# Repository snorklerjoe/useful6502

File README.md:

# Useful 6502 Machine

The goal of this project is to build a 6502-based portable machine,
running my own operating system.

## Current Status

*See the complete implementation plan and progress here: [Implemementation Plan](./IMPLEMENTATION_PLAN.md)*

PCB assembled, PIC is able to load code for the 6502 to execute, the 6502 can read/write to the 2-port SRAM.

## Hardware Goals

*These are some general points; for the full hardware specification, see here: [Hardware Specification](./HARDWARE.md)*

I want the following end goals to categorize the machine as "useful":

- At least 2 Megabytes of program memory and 2 Megabytes of data memory, of which at least 16k of memory can be used by a single process.
- Protected memory (kernel and user run modes defined by hardware checking if kernel or user code is being executed)
- PIC16 as peripheral coprocessor for fast i/o

## Software Goals

- Traps via "BRK" instruction for sys calls
- Full preemptive multitasking with up to 255 processes, round robin scheduler (maybe mlfq eventually)
- Filesystem: Tree, leaf nodes are devices or drivers.
- Driver for FAT32-formatted SD cards for easy file storage & transfer
- Standard library compatible with cc65 for creating high-level programs
- Basic UNIX-like shell utilities
- Simple web browser?
- SSH client based on DropBear?

## Faults

Faults will be detected by hardware and trigger a RESET, and the kernel will terminate the process.

## Hardware Timers

A hardware timer using the 65c22 will be used to interrupt processes with an NMI.
The kernel will maintain a global clock for user timing needs.

The PIC peripheral coprocessor may, perhaps, feature a watchdog timer to restart the kernel in the event of a crash.

## Particularly Helpful References

There are many resources that have proven themselves indispensible to the progress of his project.  
Here is a *small subset* of such resources:

- <https://www.pagetable.com/c64ref/6502/#>
- <http://www.6502.org/users/andre/index.html>
- <https://wilsonminesco.com/>
- <https://www.burtonsys.com/ps2_chapweske.htm>
- <https://www.pagetable.com/?p=1416>
- <https://github.com/commanderx16/x16-rom/>

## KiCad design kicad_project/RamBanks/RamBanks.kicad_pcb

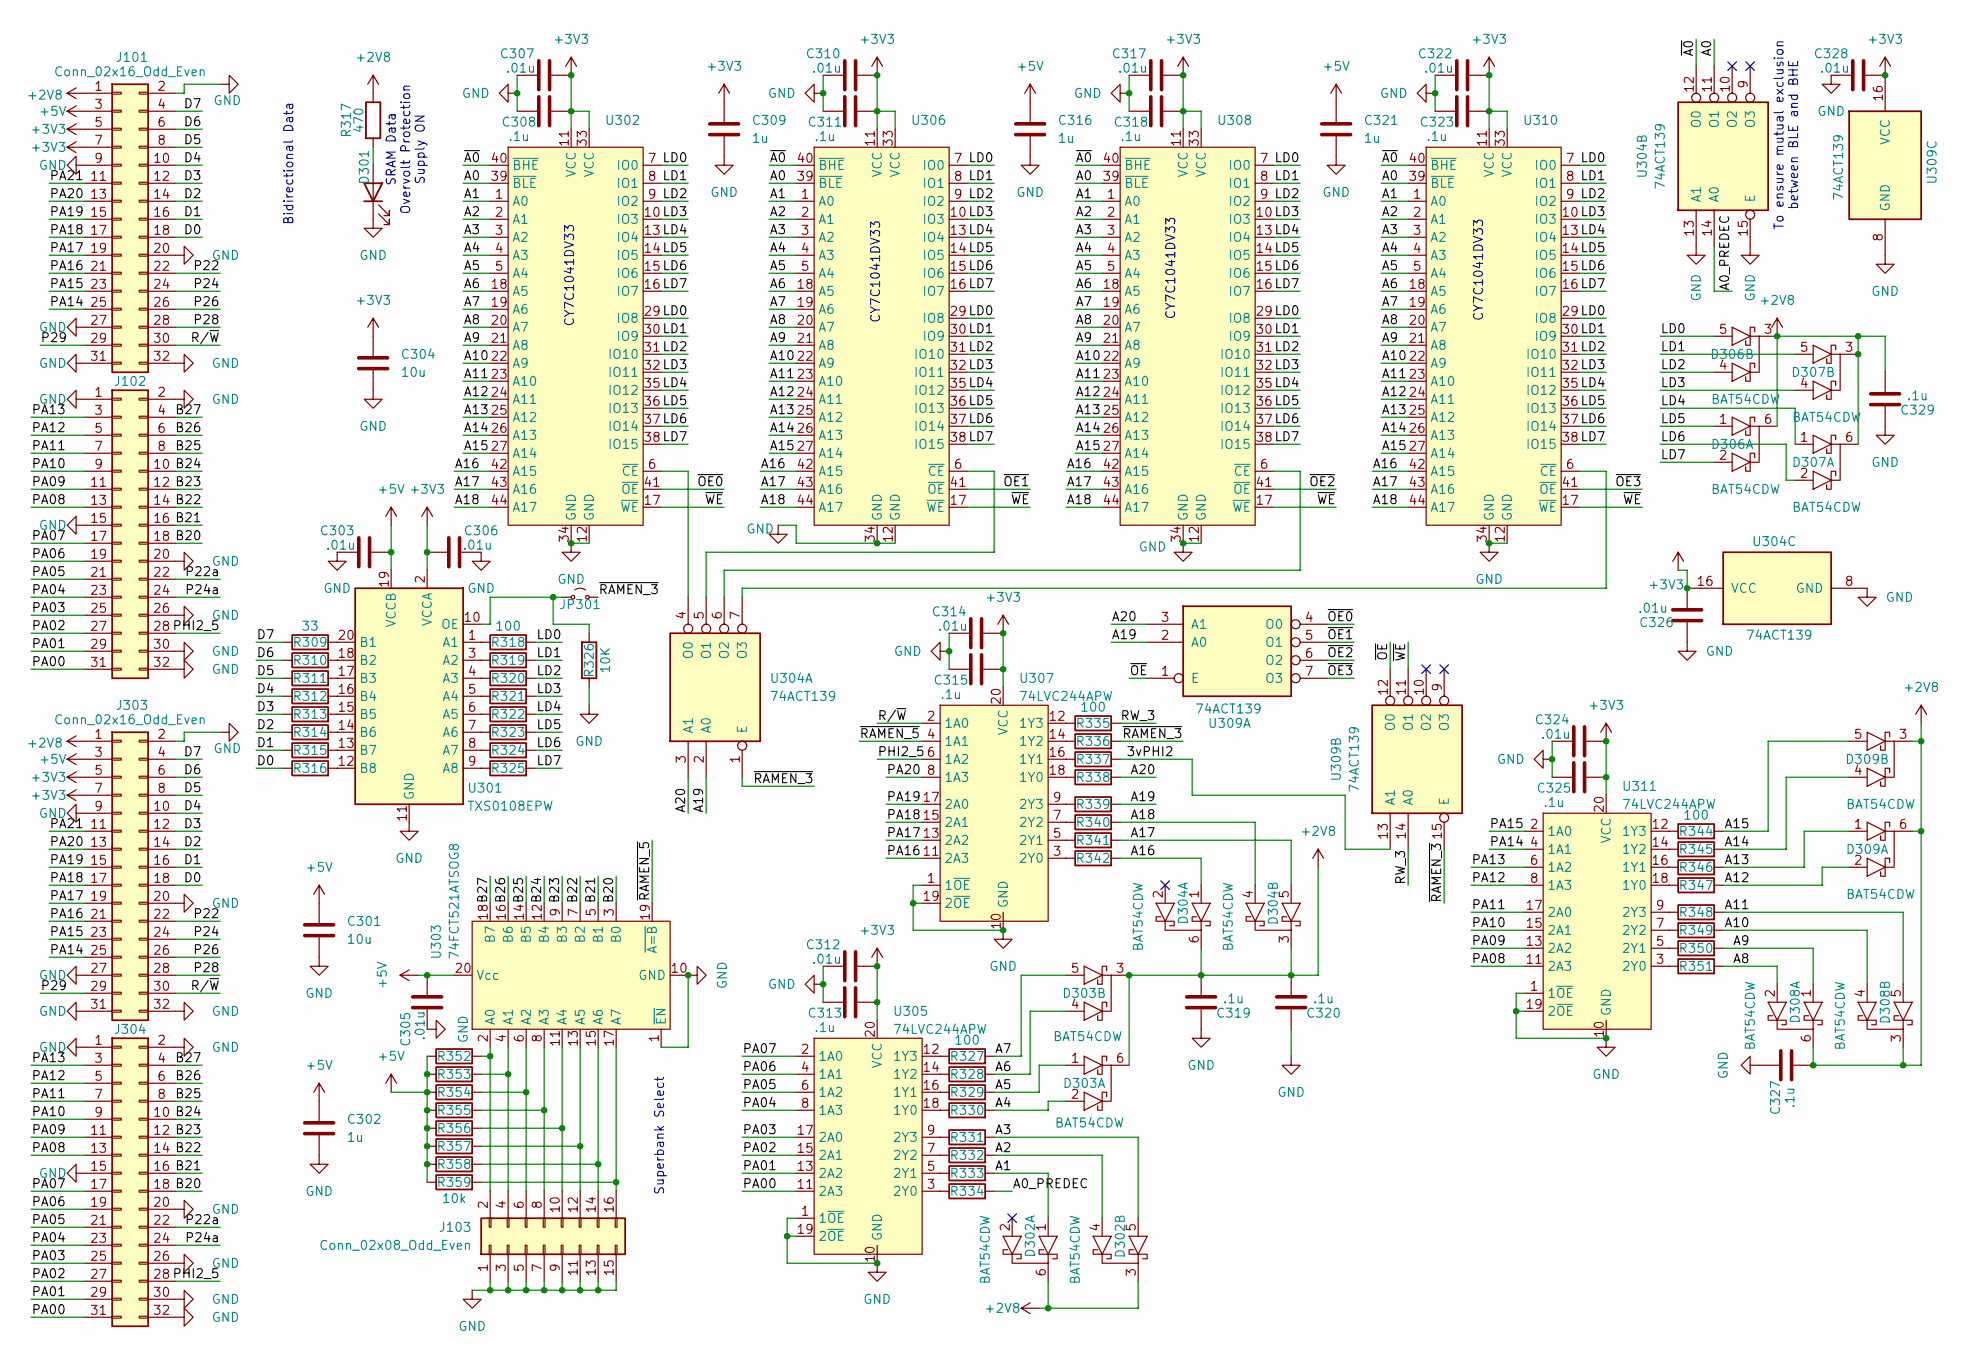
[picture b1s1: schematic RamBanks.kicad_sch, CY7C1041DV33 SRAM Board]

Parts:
C301, C304: 10u; C_0402_1005Metric
C302, C309, C316, C321: 1u; C_0402_1005Metric
C303, C305, C306, C307, C310, C312, C314, C317, C322, C324, C326, C328: .01u; C_0402_1005Metric
C308, C311, C313, C315, C318, C319, C320, C323, C325, C327, C329: .1u; C_0402_1005Metric
D301: LED; LED_0402_1005Metric
D302, D303, D304, D306, D307, D308, D309: BAT54CDW; SOT-363_SC-70-6
J101, J102: Conn_02x16_Odd_Even; PinHeader_2x16_P2.54mm_Vertical
J103: Conn_02x08_Odd_Even; PinHeader_2x08_P2.54mm_Vertical_SMD
J303, J304: Conn_02x16_Odd_Even; PinHeader_2x16_P2.54mm_Vertical_SMD
JP301: Jumper_2_Small_Open; SolderJumper-2_P1.3mm_Open_Pad1.0x1.5mm
R309, R310, R311, R312, R313, R314, R315, R316: 33; R_0402_1005Metric
R317: 470; R_0402_1005Metric
R318, R319, R320, R321, R322, R323, R324, R325, R327, R328, R329, R330, R331, R332, R333, R334, R335, R336, R337, R338, R339, R340, R341, R342, R344, R345, R346, R347, R348, R349, R350, R351: 100; R_0402_1005Metric
R326: 10K; R_0402_1005Metric
R352, R353, R354, R355, R356, R357, R358, R359: 10k; R_0402_1005Metric
U301: TXS0108EPW; TSSOP-20_4.4x6.5mm_P0.65mm
U302, U306, U308, U310: TSOP-II-44_10.16x18.41mm_P0.8mm
U303: 74FCT521ATSOG8; SOIC-20W_7.5x12.8mm_P1.27mm
U304, U309: 74ACT139; TSSOP-16_4.4x5mm_P0.65mm
U305, U307, U311: 74LVC244APW; TSSOP-20_4.4x6.5mm_P0.65mm

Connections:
+2V8: C319.1, C320.1, C327.1, C329.1, D302.3 (K2), D302.6 (K2), D303.3 (K2), D303.6 (K2), D304.3 (K2), D304.6 (K2), D306.3 (K2), D306.6 (K2), D307.3 (K2), D307.6 (K2), D308.3 (K2), D308.6 (K2), D309.3 (K2), D309.6 (K2), J101.1, J303.1, R317.1
+3V3: C304.1, C306.1, C307.1, C308.1, C309.1, C310.1, C311.1, C312.1, C313.1, C314.1, C315.1, C317.1, C318.1, C322.1, C323.1, C324.1, C325.1, C326.1, C328.1, J101.5, J101.7, J303.5, J303.7, U301.2 (VCCA), U302.11 (VCC), U302.33 (VCC), U304.16 (VCC), U305.20 (VCC), U306.11 (VCC), U306.33 (VCC), U307.20 (VCC), U308.11 (VCC), U308.33 (VCC), U309.16 (VCC), U310.11 (VCC), U310.33 (VCC), U311.20 (VCC)
+5V: C301.1, C302.1, C303.1, C305.1, C316.1, C321.1, J101.3, J303.3, R352.1, R353.1, R354.1, R355.1, R356.1, R357.1, R358.1, R359.1, U301.19 (VCCB), U303.20 (Vcc)
/3vPHI2: R337.2, U309.13 (A1)
/A0: U302.39 (~BLE), U304.11 (O1), U306.39 (~BLE), U308.39 (~BLE), U310.39 (~BLE)
/A0_PREDEC: R334.2, U304.14 (A0)
/A1: D302.1 (A01), R333.2, U302.1 (A0), U306.1 (A0), U308.1 (A0), U310.1 (A0)
/A2: D302.4 (A02), R332.2, U302.2 (A1), U306.2 (A1), U308.2 (A1), U310.2 (A1)
/A3: D302.5 (A12), R331.2, U302.3 (A2), U306.3 (A2), U308.3 (A2), U310.3 (A2)
/A4: D303.2 (A02), R330.2, U302.4 (A3), U306.4 (A3), U308.4 (A3), U310.4 (A3)
/A5: D303.1 (A01), R329.2, U302.5 (A4), U306.5 (A4), U308.5 (A4), U310.5 (A4)
/A6: D303.4 (A02), R328.2, U302.18 (A5), U306.18 (A5), U308.18 (A5), U310.18 (A5)
/A7: D303.5 (A12), R327.2, U302.19 (A6), U306.19 (A6), U308.19 (A6), U310.19 (A6)
/A8: D308.2 (A02), R351.2, U302.20 (A7), U306.20 (A7), U308.20 (A7), U310.20 (A7)
/A9: D308.1 (A01), R350.2, U302.21 (A8), U306.21 (A8), U308.21 (A8), U310.21 (A8)
/A10: D308.4 (A02), R349.2, U302.22 (A9), U306.22 (A9), U308.22 (A9), U310.22 (A9)
/A11: D308.5 (A12), R348.2, U302.23 (A10), U306.23 (A10), U308.23 (A10), U310.23 (A10)
/A12: D309.2 (A02), R347.2, U302.24 (A11), U306.24 (A11), U308.24 (A11), U310.24 (A11)
/A13: D309.1 (A01), R346.2, U302.25 (A12), U306.25 (A12), U308.25 (A12), U310.25 (A12)
/A14: D309.4 (A02), R345.2, U302.26 (A13), U306.26 (A13), U308.26 (A13), U310.26 (A13)
/A15: D309.5 (A12), R344.2, U302.27 (A14), U306.27 (A14), U308.27 (A14), U310.27 (A14)
/A16: D304.1 (A01), R342.2, U302.42 (A15), U306.42 (A15), U308.42 (A15), U310.42 (A15)
/A17: D304.5 (A12), R341.2, U302.43 (A16), U306.43 (A16), U308.43 (A16), U310.43 (A16)
/A18: D304.4 (A02), R340.2, U302.44 (A17), U306.44 (A17), U308.44 (A17), U310.44 (A17)
/A19: R339.2, U304.2 (A0), U309.2 (A0)
/A20: R338.2, U304.3 (A1), U309.3 (A1)
/B20: J102.18, J304.18, U303.3 (B0)
/B21: J102.16, J304.16, U303.5 (B1)
/B22: J102.14, J304.14, U303.7 (B2)
/B23: J102.12, J304.12, U303.9 (B3)
/B24: J102.10, J304.10, U303.12 (B4)
/B25: J102.8, J304.8, U303.14 (B5)
/B26: J102.6, J304.6, U303.16 (B6)
/B27: J102.4, J304.4, U303.18 (B7)
/D0: J101.18, J303.18, R316.1
/D1: J101.16, J303.16, R315.1
/D2: J101.14, J303.14, R314.1
/D3: J101.12, J303.12, R313.1
/D4: J101.10, J303.10, R312.1
/D5: J101.8, J303.8, R311.1
/D6: J101.6, J303.6, R310.1
/D7: J101.4, J303.4, R309.1
/LD0: D306.5 (A12), R318.2, U302.7 (IO0), U302.29 (IO8), U306.7 (IO0), U306.29 (IO8), U308.7 (IO0), U308.29 (IO8), U310.7 (IO0), U310.29 (IO8)
/LD1: D307.5 (A12), R319.2, U302.8 (IO1), U302.30 (IO9), U306.8 (IO1), U306.30 (IO9), U308.8 (IO1), U308.30 (IO9), U310.8 (IO1), U310.30 (IO9)
/LD2: D306.4 (A02), R320.2, U302.9 (IO2), U302.31 (IO10), U306.9 (IO2), U306.31 (IO10), U308.9 (IO2), U308.31 (IO10), U310.9 (IO2), U310.31 (IO10)
/LD3: D307.4 (A02), R321.2, U302.10 (IO3), U302.32 (IO11), U306.10 (IO3), U306.32 (IO11), U308.10 (IO3), U308.32 (IO11), U310.10 (IO3), U310.32 (IO11)
/LD4: D307.1 (A01), R322.2, U302.13 (IO4), U302.35 (IO12), U306.13 (IO4), U306.35 (IO12), U308.13 (IO4), U308.35 (IO12), U310.13 (IO4), U310.35 (IO12)
/LD5: D306.1 (A01), R323.2, U302.14 (IO5), U302.36 (IO13), U306.14 (IO5), U306.36 (IO13), U308.14 (IO5), U308.36 (IO13), U310.14 (IO5), U310.36 (IO13)
/LD6: D307.2 (A02), R324.2, U302.15 (IO6), U302.37 (IO14), U306.15 (IO6), U306.37 (IO14), U308.15 (IO6), U308.37 (IO14), U310.15 (IO6), U310.37 (IO14)
/LD7: D306.2 (A02), R325.2, U302.16 (IO7), U302.38 (IO15), U306.16 (IO7), U306.38 (IO15), U308.16 (IO7), U308.38 (IO15), U310.16 (IO7), U310.38 (IO15)
/P22: J101.22, J303.22
/P22a: J102.22, J304.22
/P24: J101.24, J303.24
/P24a: J102.24, J304.24
/P26: J101.26, J303.26
/P28: J101.28, J303.28
/P29: J101.29, J303.29
/PA00: J102.31, J304.31, U305.11 (2A3)
/PA01: J102.29, J304.29, U305.13 (2A2)
/PA02: J102.27, J304.27, U305.15 (2A1)
/PA03: J102.25, J304.25, U305.17 (2A0)
/PA04: J102.23, J304.23, U305.8 (1A3)
/PA05: J102.21, J304.21, U305.6 (1A2)
/PA06: J102.19, J304.19, U305.4 (1A1)
/PA07: J102.17, J304.17, U305.2 (1A0)
/PA08: J102.13, J304.13, U311.11 (2A3)
/PA09: J102.11, J304.11, U311.13 (2A2)
/PA10: J102.9, J304.9, U311.15 (2A1)
/PA11: J102.7, J304.7, U311.17 (2A0)
/PA12: J102.5, J304.5, U311.8 (1A3)
/PA13: J102.3, J304.3, U311.6 (1A2)
/PA14: J101.25, J303.25, U311.4 (1A1)
/PA15: J101.23, J303.23, U311.2 (1A0)
/PA16: J101.21, J303.21, U307.11 (2A3)
/PA17: J101.19, J303.19, U307.13 (2A2)
/PA18: J101.17, J303.17, U307.15 (2A1)
/PA19: J101.15, J303.15, U307.17 (2A0)
/PA20: J101.13, J303.13, U307.8 (1A3)
/PA21: J101.11, J303.11
/PHI2_5: J102.28, J304.28, U307.6 (1A2)
/RW_3: R335.2, U309.14 (A0)
/R/~W: J101.30, J303.30, U307.2 (1A0)
/~A0: U302.40 (~BHE), U304.12 (O0), U306.40 (~BHE), U308.40 (~BHE), U310.40 (~BHE)
/~OE0: U302.41 (~OE), U309.4 (O0)
/~OE1: U306.41 (~OE), U309.5 (O1)
/~OE2: U308.41 (~OE), U309.6 (O2)
/~OE3: U309.7 (O3), U310.41 (~OE)
/~OE: U309.1 (E), U309.12 (O0)
/~RAMEN_3: JP301.2 (B), R336.2, U304.1 (E), U309.15 (E)
/~RAMEN_5: U303.19 (~A=B), U307.4 (1A1)
/~WE: U302.17 (~WE), U306.17 (~WE), U308.17 (~WE), U309.11 (O1), U310.17 (~WE)
GND: C301.2, C302.2, C303.2, C304.2, C305.2, C306.2, C307.2, C308.2, C309.2, C310.2, C311.2, C312.2, C313.2, C314.2, C315.2, C316.2, C317.2, C318.2, C319.2, C320.2, C321.2, C322.2, C323.2, C324.2, C325.2, C326.2, C327.2, C328.2, C329.2, D301.1 (K), J101.2, J101.9, J101.20, J101.27, J101.31, J101.32, J102.1, J102.2, J102.15, J102.20, J102.26, J102.30, J102.32, J103.1, J103.3, J103.5, J103.7, J103.9, J103.11, J103.13, J103.15, J303.2, J303.9, J303.20, J303.27, J303.31, J303.32, J304.1, J304.2, J304.15, J304.20, J304.26, J304.30, J304.32, R326.1, U301.11 (GND), U302.12 (GND), U302.34 (GND), U303.1 (~EN), U303.10 (GND), U304.8 (GND), U304.13 (A1), U304.15 (E), U305.1 (1~OE), U305.10 (GND), U305.19 (2~OE), U306.12 (GND), U306.34 (GND), U307.1 (1~OE), U307.10 (GND), U307.19 (2~OE), U308.12 (GND), U308.34 (GND), U309.8 (GND), U310.12 (GND), U310.34 (GND), U311.1 (1~OE), U311.10 (GND), U311.19 (2~OE)
unnamed: D301.2 (A), R317.2
unnamed: J103.2, R352.2, U303.2 (A0)
unnamed: J103.4, R353.2, U303.4 (A1)
unnamed: J103.6, R354.2, U303.6 (A2)
unnamed: J103.8, R355.2, U303.8 (A3)
unnamed: J103.10, R356.2, U303.11 (A4)
unnamed: J103.12, R357.2, U303.13 (A5)
unnamed: J103.14, R358.2, U303.15 (A6)
unnamed: J103.16, R359.2, U303.17 (A7)
unnamed: JP301.1 (A), R326.2, U301.10 (OE)
unnamed: R318.1, U301.1 (A1)
unnamed: R319.1, U301.3 (A2)
unnamed: R320.1, U301.4 (A3)
unnamed: R321.1, U301.5 (A4)
unnamed: R322.1, U301.6 (A5)
unnamed: R323.1, U301.7 (A6)
unnamed: R324.1, U301.8 (A7)
unnamed: R325.1, U301.9 (A8)
unnamed: R309.2, U301.20 (B1)
unnamed: R310.2, U301.18 (B2)
unnamed: R311.2, U301.17 (B3)
unnamed: R312.2, U301.16 (B4)
unnamed: R313.2, U301.15 (B5)
unnamed: R314.2, U301.14 (B6)
unnamed: R315.2, U301.13 (B7)
unnamed: R316.2, U301.12 (B8)
unnamed: U302.6 (~CE), U304.4 (O0)
unnamed: U304.5 (O1), U306.6 (~CE)
unnamed: U304.6 (O2), U308.6 (~CE)
unnamed: U304.7 (O3), U310.6 (~CE)
unnamed: R330.1, U305.18 (1Y0)
unnamed: R329.1, U305.16 (1Y1)
unnamed: R328.1, U305.14 (1Y2)
unnamed: R327.1, U305.12 (1Y3)
unnamed: R334.1, U305.3 (2Y0)
unnamed: R333.1, U305.5 (2Y1)
unnamed: R332.1, U305.7 (2Y2)
unnamed: R331.1, U305.9 (2Y3)
unnamed: R338.1, U307.18 (1Y0)
unnamed: R337.1, U307.16 (1Y1)
unnamed: R336.1, U307.14 (1Y2)
unnamed: R335.1, U307.12 (1Y3)
unnamed: R342.1, U307.3 (2Y0)
unnamed: R341.1, U307.5 (2Y1)
unnamed: R340.1, U307.7 (2Y2)
unnamed: R339.1, U307.9 (2Y3)
unnamed: R347.1, U311.18 (1Y0)
unnamed: R346.1, U311.16 (1Y1)
unnamed: R345.1, U311.14 (1Y2)
unnamed: R344.1, U311.12 (1Y3)
unnamed: R351.1, U311.3 (2Y0)
unnamed: R350.1, U311.5 (2Y1)
unnamed: R349.1, U311.7 (2Y2)
unnamed: R348.1, U311.9 (2Y3)

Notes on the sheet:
SRAM Data Overvolt Protection Supply ON
Superbank Select
CY7C1041DV33
To ensure mutual exclusion between BLE and BHE
Bidirectional Data

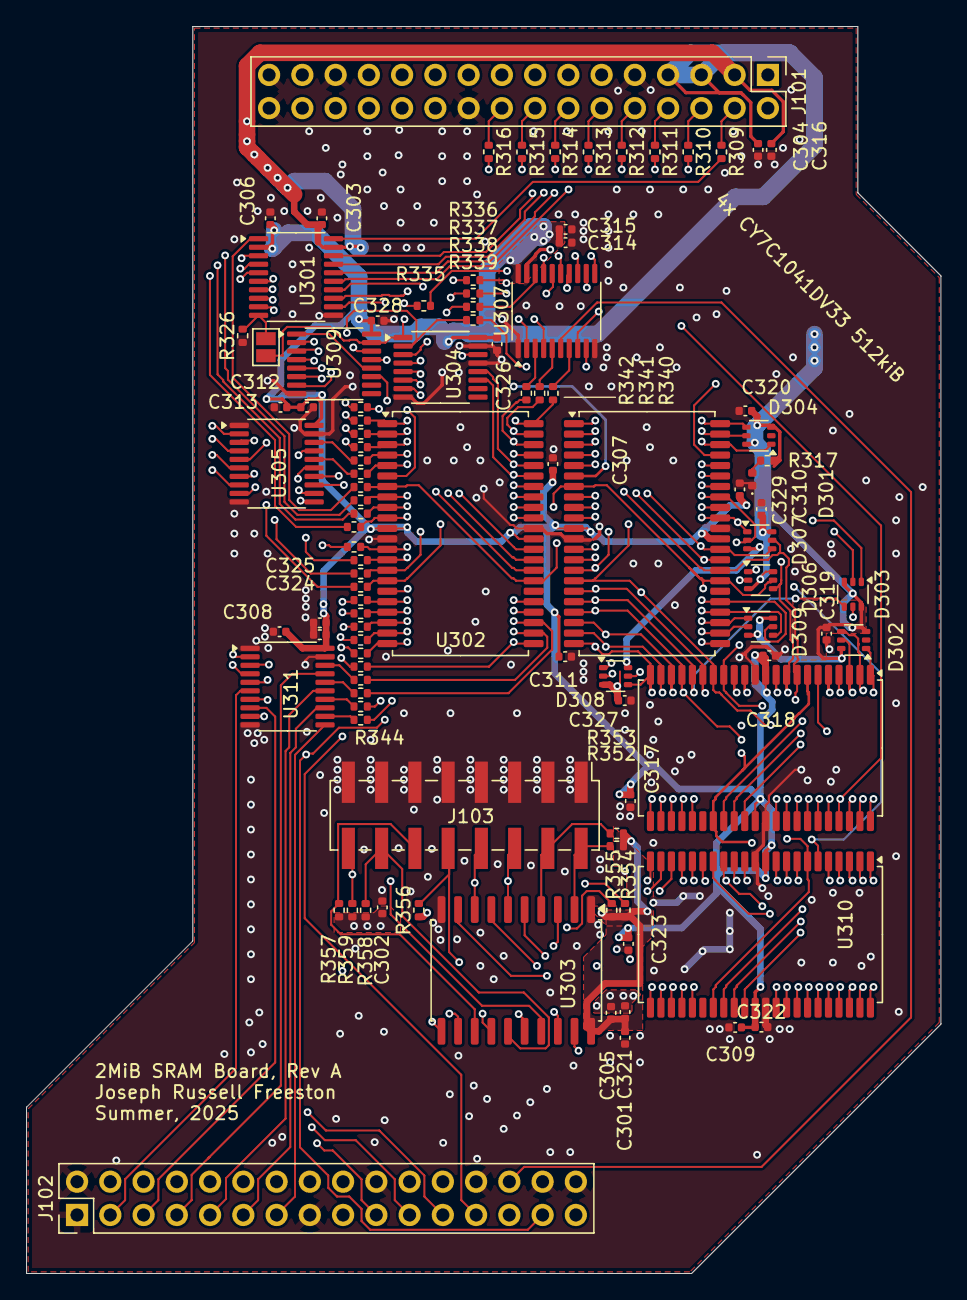
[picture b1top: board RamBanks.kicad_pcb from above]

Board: 4 copper layers, 69.8 x 95.2 mm, 102 parts (0 on the bottom side), 138 nets.

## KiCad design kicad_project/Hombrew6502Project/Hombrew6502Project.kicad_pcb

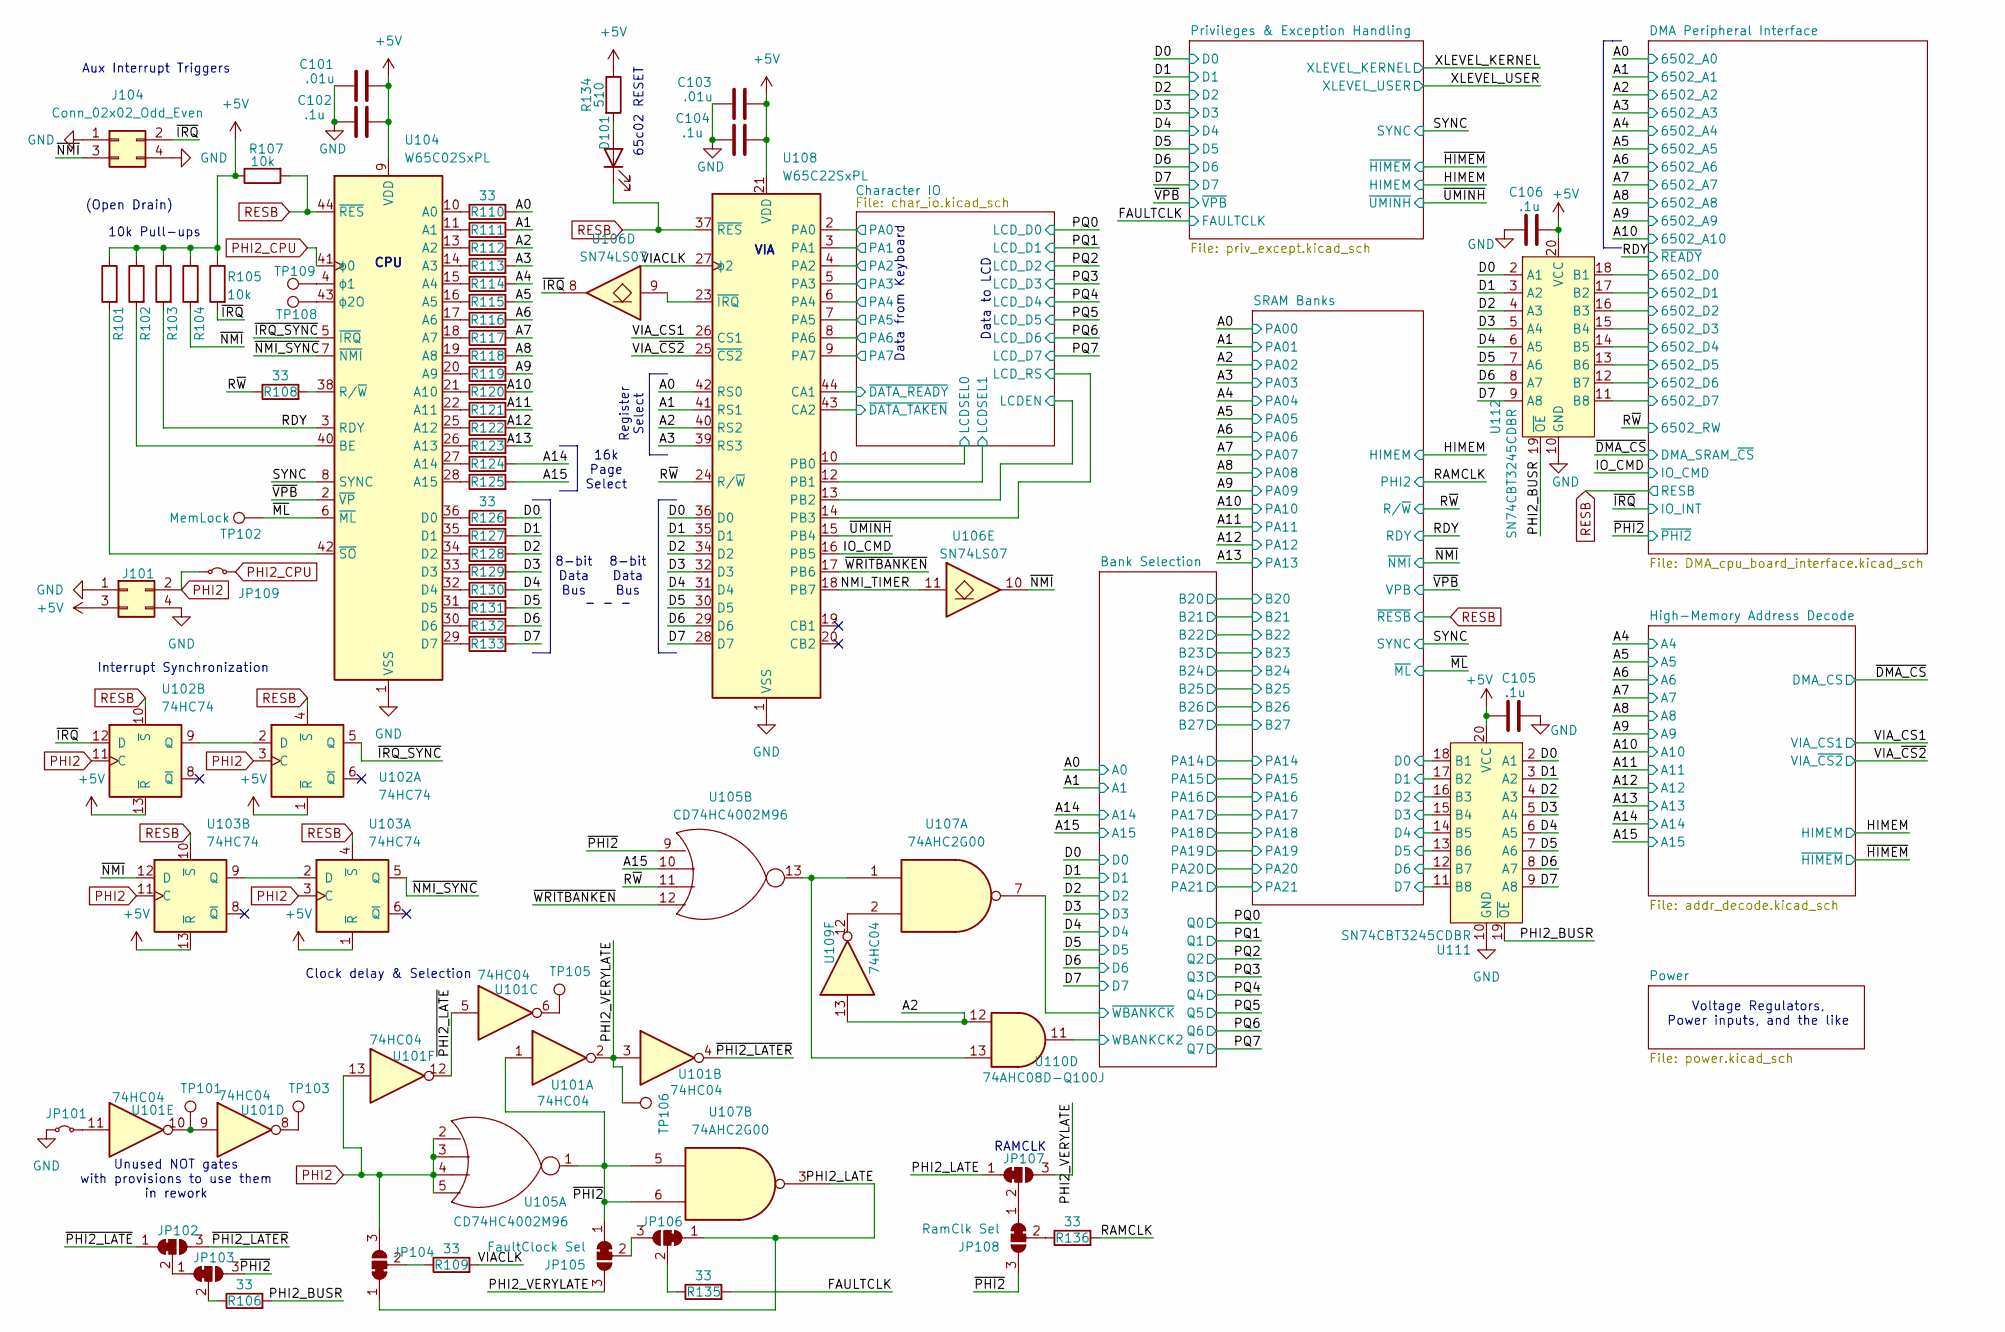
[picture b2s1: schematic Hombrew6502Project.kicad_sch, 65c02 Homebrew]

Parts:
C101, C103: .01u; C_0402_1005Metric
C102, C104, C105, C106: .1u; C_0402_1005Metric
D101: LED; LED_0402_1005Metric
J101, J104: Conn_02x02_Odd_Even; PinHeader_2x02_P2.54mm_Vertical_SMD
JP101, JP109: Jumper_2_Small_Bridged; SolderJumper-2_P1.3mm_Bridged2Bar_Pad1.0x1.5mm
JP102, JP103, JP105, JP106, JP107: FaultClock Sel; SolderJumper-3_P1.3mm_Bridged12_Pad1.0x1.5mm
JP104: SolderJumper_3_Bridged12; SolderJumper-3_P1.3mm_Bridged12_Pad1.0x1.5mm
JP108: RamClk Sel; SolderJumper-3_P1.3mm_Bridged12_Pad1.0x1.5mm
R101, R102, R103, R104, R105, R107: 10k; R_0402_1005Metric
R106, R108, R109, R110, R111, R112, R113, R114, R115, R116, R117, R118, R119, R120, R121, R122, R123, R124, R125, R126, R127, R128, R129, R130, R131, R132, R133, R135, R136: 33; R_0402_1005Metric
R134: 510; R_0402_1005Metric
TP101, TP103: TestPoint; TestPoint_Pad_D2.5mm
TP102: MemLock; TestPoint_Pad_D1.5mm
TP105, TP106: TestPoint; TestPoint_Pad_D1.5mm
TP108: phi2O; TestPoint_Pad_D1.5mm
TP109: phi1; TestPoint_Pad_D1.5mm
U101, U109: 74HC04; SOIC-14_3.9x8.7mm_P1.27mm
U102, U103: 74HC74; SOIC-14_3.9x8.7mm_P1.27mm
U104: W65C02SxPL; PLCC-44
U105: CD74HC4002M96; SOIC-14_3.9x8.7mm_P1.27mm
U106: SN74LS07; SOIC-14_3.9x8.7mm_P1.27mm
U107: 74AHC2G00; TSSOP-8_3x3mm_P0.65mm
U108: W65C22SxPL; PLCC-44
U110: 74AHC08D-Q100J; SOIC-14_3.9x8.7mm_P1.27mm
U111, U112: SN74CBT3245CDBR; SSOP-20_5.3x7.2mm_P0.65mm

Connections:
+5V: C101.1, C102.1, C103.1, C104.1, C105.1, C106.1, J101.3, R101.1, R102.1, R103.1, R104.1, R105.1, R107.1, R134.1, U102.1 (~R), U102.13 (~R), U103.1 (~R), U103.13 (~R), U104.9 (VDD), U104.37 (VDD), U108.21 (VDD), U111.20 (VCC), U112.20 (VCC); also elsewhere on the board
/A0: R110.2, U108.42 (RS0); also elsewhere on the board
/A1: R111.2, U108.41 (RS1); also elsewhere on the board
/A2: R112.2, U108.40 (RS2), U109.13, U110.12; also elsewhere on the board
/A3: R113.2, U108.39 (RS3); also elsewhere on the board
/A4: R114.2; also elsewhere on the board
/A5: R115.2; also elsewhere on the board
/A6: R116.2; also elsewhere on the board
/A7: R117.2; also elsewhere on the board
/A8: R118.2; also elsewhere on the board
/A9: R119.2; also elsewhere on the board
/A10: R120.2; also elsewhere on the board
/A11: R121.2; also elsewhere on the board
/A12: R122.2; also elsewhere on the board
/A13: R123.2; also elsewhere on the board
/A14: R124.2; also elsewhere on the board
/A15: R125.2, U105.10; also elsewhere on the board
/Bank Selection/WBANKCK2: U110.11; also elsewhere on the board
/Bank Selection/~WBANKCK: U107.7; also elsewhere on the board
/Character IO/LCDEN: U108.13 (PB2); also elsewhere on the board
/Character IO/LCDSEL0: U108.10 (PB0); also elsewhere on the board
/Character IO/LCDSEL1: U108.12 (PB1); also elsewhere on the board
/Character IO/LCD_RS: U108.14 (PB3); also elsewhere on the board
/Character IO/PA0: U108.2 (PA0); also elsewhere on the board
/Character IO/PA1: U108.3 (PA1); also elsewhere on the board
/Character IO/PA2: U108.4 (PA2); also elsewhere on the board
/Character IO/PA3: U108.5 (PA3); also elsewhere on the board
/Character IO/PA4: U108.6 (PA4); also elsewhere on the board
/Character IO/PA5: U108.7 (PA5); also elsewhere on the board
/Character IO/PA6: U108.8 (PA6); also elsewhere on the board
/Character IO/PA7: U108.9 (PA7); also elsewhere on the board
/Character IO/~DATA_READY: U108.44 (CA1); also elsewhere on the board
/Character IO/~DATA_TAKEN: U108.43 (CA2); also elsewhere on the board
/D0: R126.2, U108.36 (D0), U111.2 (A1), U112.2 (A1); also elsewhere on the board
/D1: R127.2, U108.35 (D1), U111.3 (A2), U112.3 (A2); also elsewhere on the board
/D2: R128.2, U108.34 (D2), U111.4 (A3), U112.4 (A3); also elsewhere on the board
/D3: R129.2, U108.32 (D3), U111.5 (A4), U112.5 (A4); also elsewhere on the board
/D4: R130.2, U108.31 (D4), U111.6 (A5), U112.6 (A5); also elsewhere on the board
/D5: R131.2, U108.30 (D5), U111.7 (A6), U112.7 (A6); also elsewhere on the board
/D6: R132.2, U108.29 (D6), U111.8 (A7), U112.8 (A7); also elsewhere on the board
/D7: R133.2, U108.28 (D7), U111.9 (A8), U112.9 (A8); also elsewhere on the board
/DMA Peripheral Interface/6502_D0: U112.18 (B1); also elsewhere on the board
/DMA Peripheral Interface/6502_D1: U112.17 (B2); also elsewhere on the board
/DMA Peripheral Interface/6502_D2: U112.16 (B3); also elsewhere on the board
/DMA Peripheral Interface/6502_D3: U112.15 (B4); also elsewhere on the board
/DMA Peripheral Interface/6502_D4: U112.14 (B5); also elsewhere on the board
/DMA Peripheral Interface/6502_D5: U112.13 (B6); also elsewhere on the board
/DMA Peripheral Interface/6502_D6: U112.12 (B7); also elsewhere on the board
/DMA Peripheral Interface/6502_D7: U112.11 (B8); also elsewhere on the board
/FAULTCLK: R135.2; also elsewhere on the board
/IO_CMD: U108.16 (PB5); also elsewhere on the board
/NMI_TIMER: U106.11, U108.18 (PB7)
/PHI2_BUSR: R106.2, U111.19 (~OE), U112.19 (~OE)
/PHI2_LATE: JP104.1 (A), JP106.1 (A), JP107.1 (A), U107.3
/PHI2_VERYLATE: JP105.3 (B), JP107.3 (B), TP106.1, U101.2, U101.3
/RAMCLK: R136.2; also elsewhere on the board
/RDY: R103.2, U104.3 (RDY); also elsewhere on the board
/R~W: R108.1, U105.11, U108.24 (R/~W); also elsewhere on the board
/SRAM Banks/D0: U111.18 (B1); also elsewhere on the board
/SRAM Banks/D1: U111.17 (B2); also elsewhere on the board
/SRAM Banks/D2: U111.16 (B3); also elsewhere on the board
/SRAM Banks/D3: U111.15 (B4); also elsewhere on the board
/SRAM Banks/D4: U111.14 (B5); also elsewhere on the board
/SRAM Banks/D5: U111.13 (B6); also elsewhere on the board
/SRAM Banks/D6: U111.12 (B7); also elsewhere on the board
/SRAM Banks/D7: U111.11 (B8); also elsewhere on the board
/SYNC: U104.8 (SYNC); also elsewhere on the board
/VIACLK: R109.2, U108.27 (ϕ2)
/VIA_CS1: U108.26 (CS1); also elsewhere on the board
/VIA_~CS2: U108.25 (~CS2); also elsewhere on the board
/~IRQ_SYNC: U102.5 (Q), U104.5 (~IRQ)
/~IRQ: J104.2, R105.2, U102.12 (D), U106.8; also elsewhere on the board
/~ML: TP102.1, U104.6 (~ML); also elsewhere on the board
/~NMI_SYNC: U103.5 (Q), U104.7 (~NMI)
/~NMI: J104.3, R104.2, U103.12 (D), U106.10; also elsewhere on the board
/~PHI2_LATER: JP102.3 (B), U101.4
/~PHI2_LATE: JP102.1 (A), U101.5, U101.12
/~PHI2: JP103.3 (B), JP105.1 (A), JP108.3 (B), U101.1, U105.1, U105.9, U107.5, U107.6; also elsewhere on the board
/~UMINH: U108.15 (PB4); also elsewhere on the board
/~VPB: U104.2 (~VP); also elsewhere on the board
/~WRITBANKEN: U105.12, U108.17 (PB6)
GND: C101.2, C102.2, C103.2, C104.2, C105.2, C106.2, J101.1, J101.4, J104.1, J104.4, JP101.1 (A), U104.1 (VSS), U104.23 (VSS), U104.24 (VSS), U108.1 (VSS), U111.10 (GND), U112.10 (GND); also elsewhere on the board
unnamed: D101.2 (A), R134.2
unnamed: JP101.2 (B), U101.11
unnamed: JP102.2 (C), JP103.1 (A)
unnamed: JP103.2 (C), R106.1
unnamed: JP104.2 (C), R109.1
unnamed: JP105.2 (C), JP106.3 (B)
unnamed: JP106.2 (C), R135.1
unnamed: JP107.2 (C), JP108.1 (A)
unnamed: JP108.2 (C), R136.1
unnamed: TP101.1, U101.9, U101.10
unnamed: TP103.1, U101.8
unnamed: TP105.1, U101.6
unnamed: U102.2 (D), U102.9 (Q)
unnamed: U103.2 (D), U103.9 (Q)
unnamed: R110.1, U104.10 (A0)
unnamed: R111.1, U104.11 (A1)
unnamed: R112.1, U104.13 (A2)
unnamed: R113.1, U104.14 (A3)
unnamed: R114.1, U104.15 (A4)
unnamed: R115.1, U104.16 (A5)
unnamed: R116.1, U104.17 (A6)
unnamed: R117.1, U104.18 (A7)
unnamed: R118.1, U104.19 (A8)
unnamed: R119.1, U104.20 (A9)
unnamed: R120.1, U104.21 (A10)
unnamed: R121.1, U104.22 (A11)
unnamed: R122.1, U104.25 (A12)
unnamed: R123.1, U104.26 (A13)
unnamed: R124.1, U104.27 (A14)
unnamed: R125.1, U104.28 (A15)
unnamed: R102.2, U104.40 (BE)
unnamed: R126.1, U104.36 (D0)
unnamed: R127.1, U104.35 (D1)
unnamed: R128.1, U104.34 (D2)
unnamed: R129.1, U104.33 (D3)
unnamed: R130.1, U104.32 (D4)
unnamed: R131.1, U104.31 (D5)
unnamed: R132.1, U104.30 (D6)
unnamed: R133.1, U104.29 (D7)
unnamed: R108.2, U104.38 (R/~W)
unnamed: R101.2, U104.42 (~SO)
unnamed: TP109.1, U104.4 (ϕ1)
unnamed: TP108.1, U104.43 (ϕ2O)
unnamed: U105.13, U107.1, U110.13
unnamed: U107.2, U109.12
unnamed: U106.9, U108.23 (~IRQ)
PHI2: J101.2, JP104.3 (B), JP109.1 (A), U101.13, U102.3 (C), U102.11 (C), U103.3 (C), U103.11 (C), U105.2, U105.3, U105.4, U105.5
PHI2_CPU: JP109.2 (B), U104.41 (ϕ0)
RESB: D101.1 (K), R107.2, U102.4 (~S), U102.10 (~S), U103.4 (~S), U103.10 (~S), U104.44 (~RES), U108.37 (~RES); also elsewhere on the board

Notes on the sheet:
Data to LCD
65c02 RESET
(Open Drain)
VIA
10k Pull-ups
Clock delay & Selection
8-bit Data Bus
- - -
CPU
Register Select
RAMCLK
Data from Keyboard
Aux Interrupt Triggers
Unused NOT gates with provisions to use them in rework
16k Page Select
Interrupt Synchronization
Voltage Regulators, Power inputs, and the like

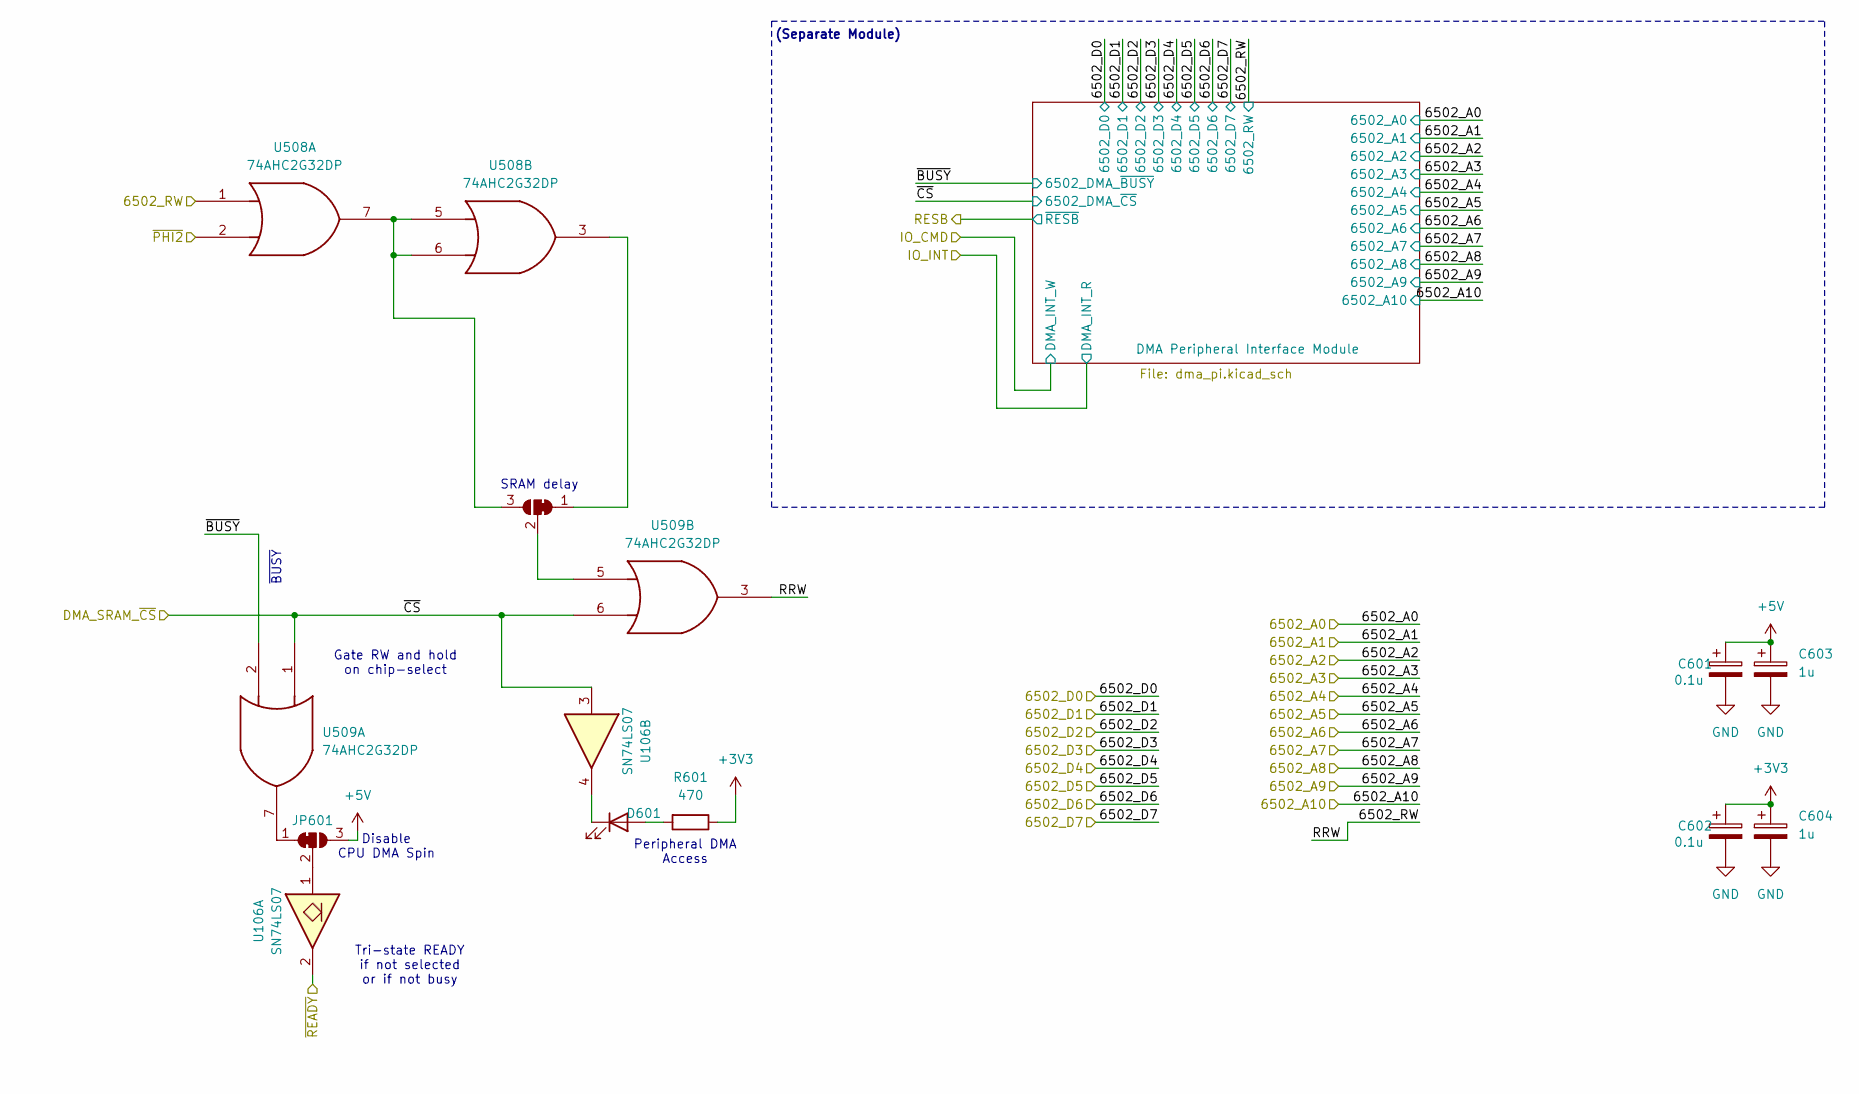
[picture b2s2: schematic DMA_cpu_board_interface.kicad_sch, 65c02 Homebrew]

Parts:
C601, C602: 0.1u; C_0402_1005Metric
C603, C604: 1u; C_0402_1005Metric
D601: LED; LED_0402_1005Metric
JP601, JP602: SolderJumper_3_Bridged12; SolderJumper-3_P1.3mm_Bridged12_Pad1.0x1.5mm
R601: 470; R_0402_1005Metric
U106: SN74LS07; SOIC-14_3.9x8.7mm_P1.27mm
U508, U509: 74AHC2G32DP; TSSOP-8_3x3mm_P0.65mm

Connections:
+3V3: C602.1, C604.1, R601.1; also elsewhere on the board
+5V: C601.1, C603.1, JP601.3 (B); also elsewhere on the board
/DMA Peripheral Interface/~BUSY: U509.2; also elsewhere on the board
/RDY: U106.2; also elsewhere on the board
/R~W: U508.1, U509.3; also elsewhere on the board
/~DMA_CS: U106.3, U509.1, U509.6; also elsewhere on the board
/~PHI2: U508.2; also elsewhere on the board
GND: C601.2, C602.2, C603.2, C604.2; also elsewhere on the board
unnamed: D601.2 (A), R601.2
unnamed: D601.1 (K), U106.4
unnamed: JP601.1 (A), U509.7
unnamed: JP601.2 (C), U106.1
unnamed: JP602.1 (A), U508.3
unnamed: JP602.3 (B), U508.5, U508.6, U508.7
unnamed: JP602.2 (C), U509.5

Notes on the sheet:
SRAM delay
Gate RW and hold on chip-select
Tri-state READY if not selected or if not busy
(Separate Module)
~{BUSY}
Disable CPU DMA Spin
Peripheral DMA Access

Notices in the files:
src/PICBridge-firmware/mcc_generated_files/system/pins.h:
© [2025] Microchip Technology Inc. and its subsidiaries.
